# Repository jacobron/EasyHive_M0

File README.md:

# EasyHive_M0
M0-Board Code (Arduino C++) and Hardware Files V1.3

This Board is designed for the purpose of remote and off-grid temperature and weight measurements.

# Features

* ADS1232 ADC-IC for weight reading up to two load-cells
* ATSAMD21G - CortexM0 Microcontroller - programmable with Arduino Software
* Ublox SaraN200 NB-IOT Chip for sending data via narrowband-LTE
* BQ24072 charging IC for USB/Solar and battery temperature monitoring
* DS18B20 temperatur sensor von Maxim Integrated
* Piezo Buzzer and RGB LED for user communication

The board features additional connections for I2S and I2C sensors, which are not used yet.

# copyright
Software: GPL 3.0 and following versions

Hardware: CERN OHL 1.2 and following versions

This files are distributed in the hope that it will be useful,
but WITHOUT ANY WARRANTY; without even the implied warranty of
MERCHANTABILITY or FITNESS FOR A PARTICULAR PURPOSE.
See the GNU General Public License for more details.

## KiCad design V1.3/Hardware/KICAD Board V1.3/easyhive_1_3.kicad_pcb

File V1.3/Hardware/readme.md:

# additional information
* steuckliste is missing some LEDs - we won't use them in production run as nobody see's them in the box ;-)

# copyright
CERN OHL 1.2 and following versions

This files are distributed in the hope that it will be useful,
but WITHOUT ANY WARRANTY; without even the implied warranty of
MERCHANTABILITY or FITNESS FOR A PARTICULAR PURPOSE.
See the GNU General Public License for more details.

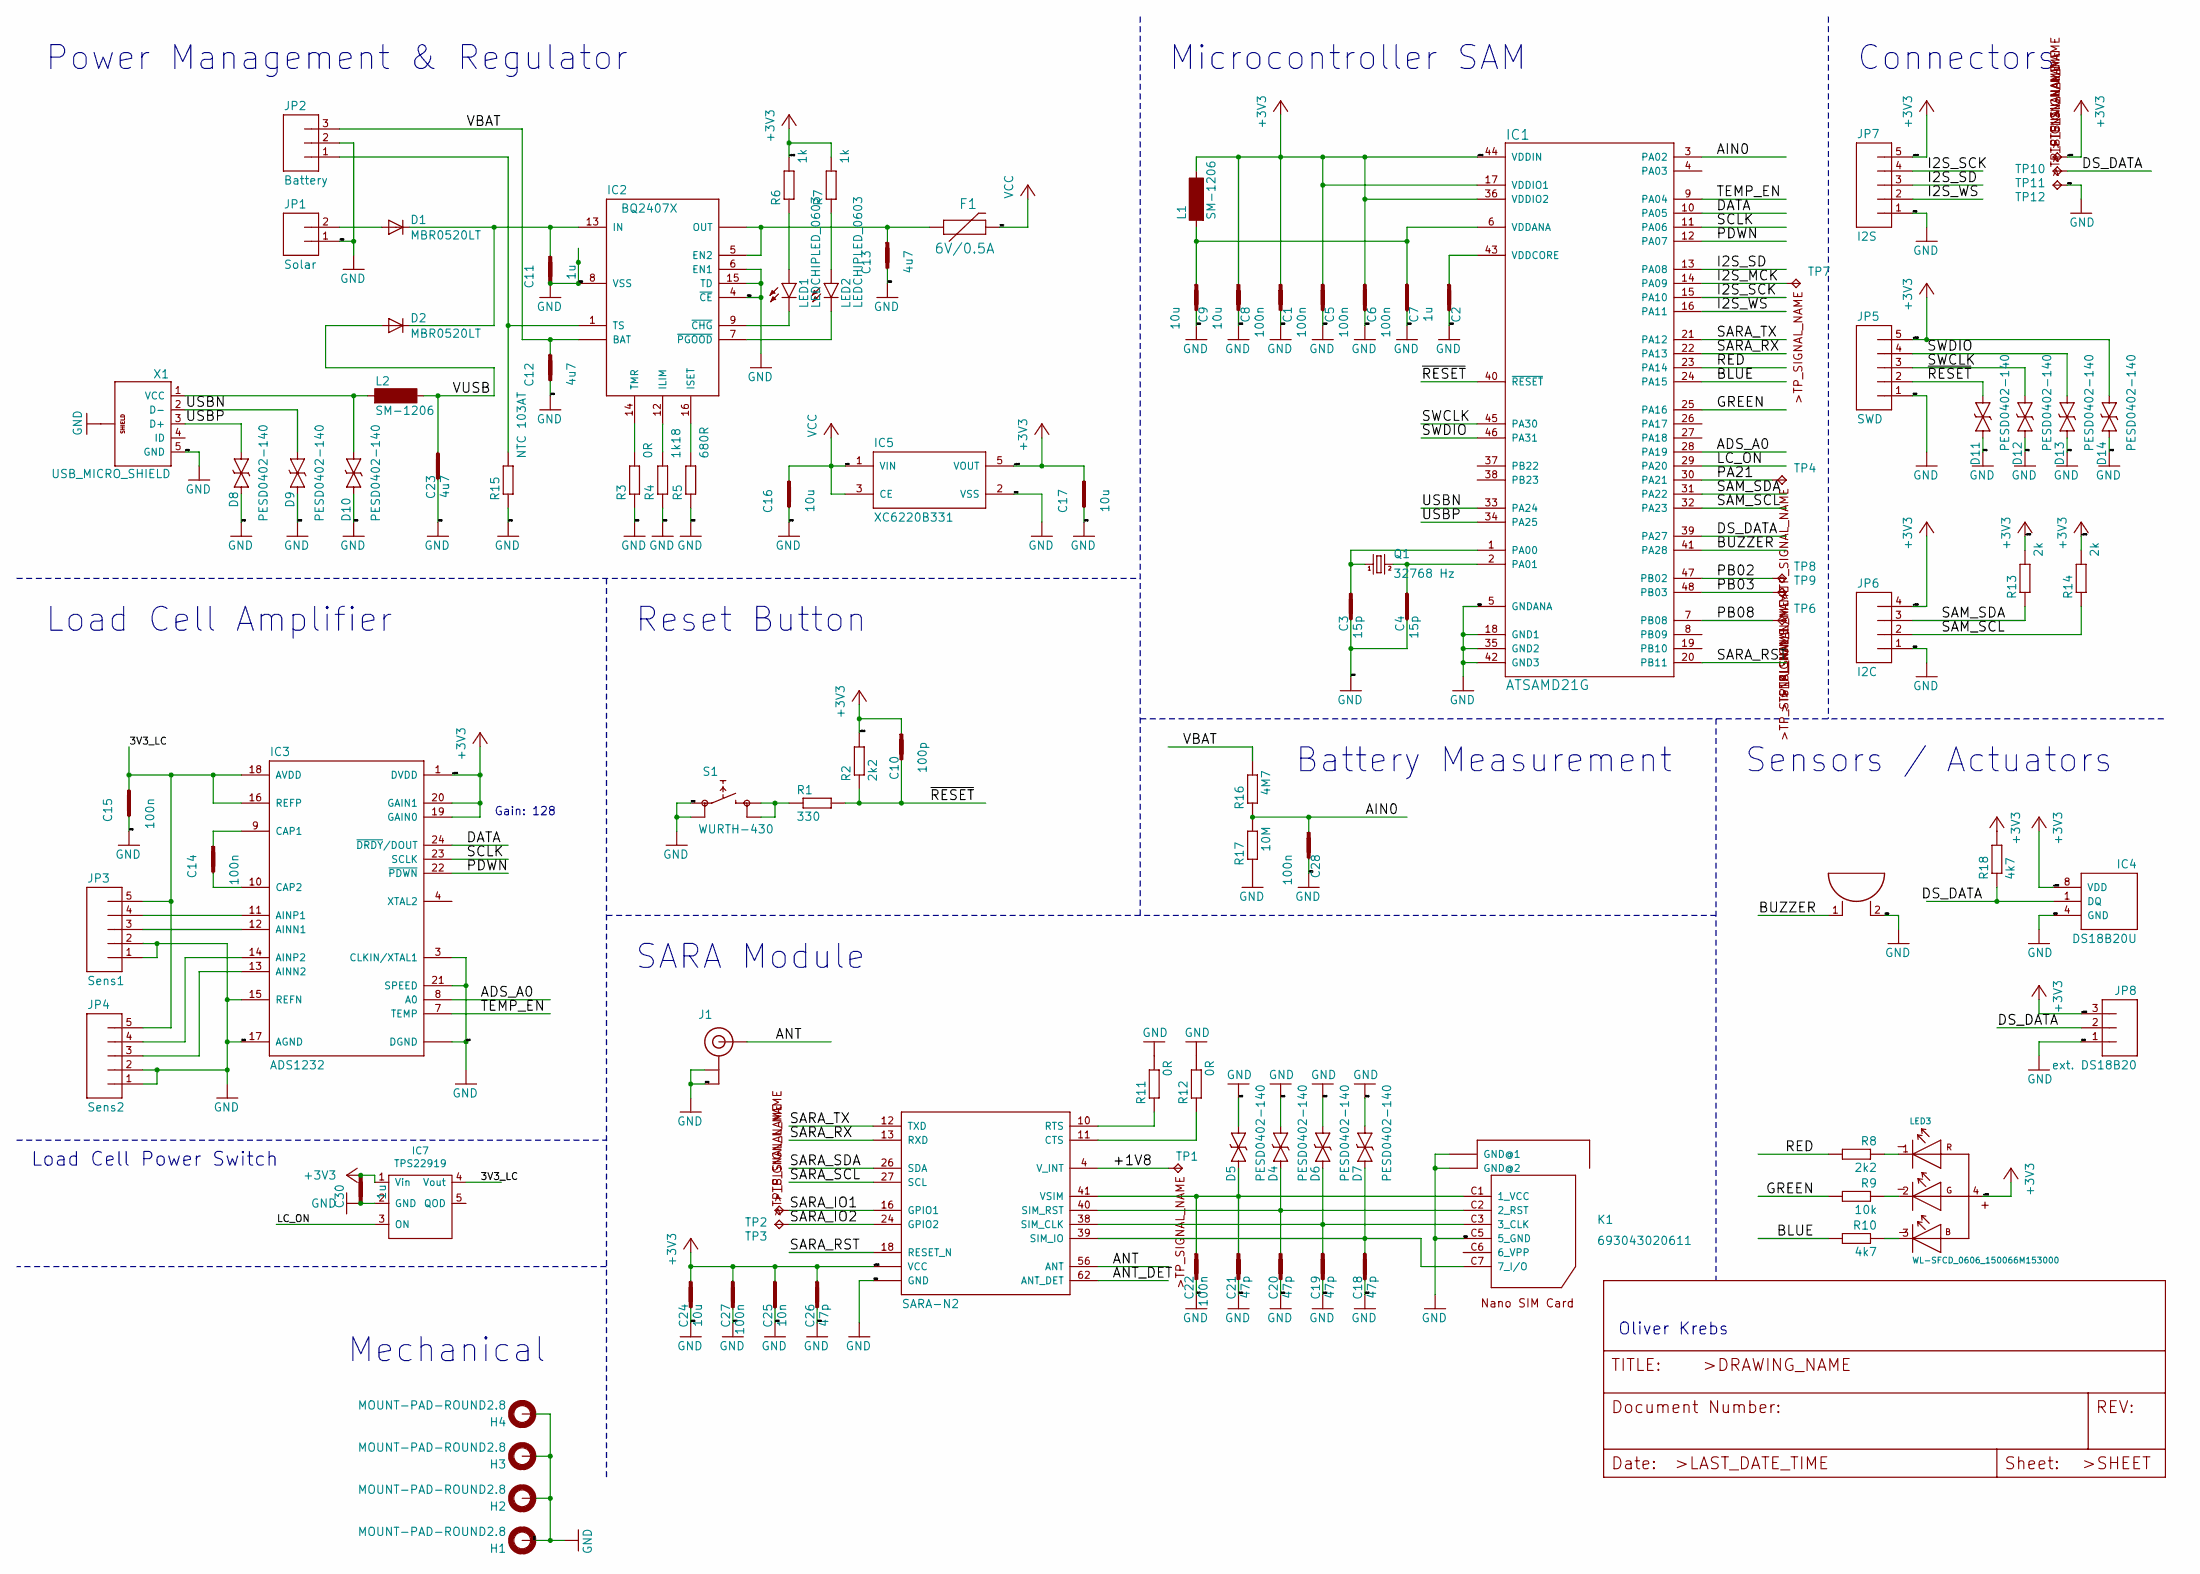
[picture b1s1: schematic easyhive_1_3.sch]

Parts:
C1, C5, C6, C7, C14, C15, C22, C27, C28: 100n; C0402
C2, C11, C30: 1u; C0402
C3, C4: 15p; C0402
C8, C9, C16, C17, C24: 10u; C0402
C10: 100p; C0402
C12, C13, C23: 4u7; C0402
C18, C19, C20, C21, C26: 47p; C0402
C25: 10n; C0402
D1, D2: MBR0520LT; SOD123
D4, D5, D6, D7, D8, D9, D10, D11, D12, D13, D14: PESD0402-140; 0402-TVS
F1: 6V/0.5A; 1206
H1, H2, H3, H4: MOUNT-PAD-ROUND2.8; 2,8-PAD
IC1: ATSAMD21G; TQFP48
IC2: BQ2407X; VQFN16
IC3: ADS1232; TSSOP24
IC4: DS18B20U; UMAX8
IC5: XC6220B331; SOT25
IC6: SARA-N2
IC7: TPS22919; sot-sc70-6
J1: U.FL
JP1: Solar; 1X02_2MM
JP2: Battery; 1X03-2MM
JP3: Sens1; 1X05-2MM
JP4: Sens2; 1X05-2MM
JP5: SWD; 1X05-2MM
JP6: I2C; 1X04-2MM
JP7: I2S; 1X05-2MM
JP8: ext. DS18B20; 1X03-2MM
K1: 693043020611
L1, L2: SM-1206
LED1, LED2: LEDCHIPLED_0603; CHIPLED_0603
LED3: WL-SFCD_0606_150066M153000; WL-SFCX_0606
P1: PKMCS; PKMCS_BUZZER
Q1: 32768 Hz; FC135
R1: 330; C0402
R2, R8: 2k2; C0402
R3, R11, R12: 0R; C0402
R4: 1k18; C0402
R5: 680R; C0402
R6, R7: 1k; C0402
R9: 10k; C0402
R10, R18: 4k7; C0402
R13, R14: 2k; C0402
R15: NTC 103AT; C0402
R16: 4M7; C0402
R17: 10M; C0402
S1: WURTH-430
TP1, TP2, TP3, TP4, TP6, TP7, TP8, TP9, TP10, TP11, TP12: TPTP08R; TP08R
X1: USB_MICRO_SHIELD; USBMICRO

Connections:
+3V3: C1.1, C5.1, C6.1, C8.1, C10.1, C17.1, C24.1, C25.1, C26.1, C27.1, C30.1, D14.P$2 (C), IC1.17 (VDDIO1), IC1.36 (VDDIO2), IC1.44 (VDDIN), IC3.1 (DVDD), IC3.19 (GAIN0), IC3.20 (GAIN1), IC4.8 (VDD), IC5.5 (VOUT), IC6.51 (VCC), IC6.52 (VCC), IC6.53 (VCC), IC7.1 (Vin), JP5.5, JP6.4, JP7.5, JP8.3, L1.2, LED3.4, R2.2, R6.2, R7.2, R13.2, R14.2, R18.2, TP10.TP
/3V3_LC: C15.1, IC3.16 (REFP), IC3.18 (AVDD), IC7.4 (Vout), JP3.5, JP4.5
/+1V8: IC6.4 (V_INT), TP1.TP
/ADS_A0: IC1.28 (PA19), IC3.8 (A0)
/AIN0: C28.1, IC1.3 (PA02), R16.1, R17.2
/ANT: IC6.56 (ANT), J1.P$3 (SIGNAL)
/ANT_DET: IC6.62 (ANT_DET)
/BLUE: IC1.24 (PA15), R10.2
/BUZZER: IC1.41 (PA28), P1.1
/DATA: IC1.10 (PA05), IC3.24 (~DRDY~/DOUT)
/DS_DATA: IC1.39 (PA27), IC4.1 (DQ), JP8.2, R18.1, TP11.TP
/GREEN: IC1.25 (PA16), R9.2
/I2S_MCK: IC1.14 (PA09), TP7.TP
/I2S_SCK: IC1.15 (PA10), JP7.4
/I2S_SD: IC1.13 (PA08), JP7.3
/I2S_WS: IC1.16 (PA11), JP7.2
/LC_ON: IC1.29 (PA20), IC7.3 (ON)
/PA21: IC1.30 (PA21), TP4.TP
/PB02: IC1.47 (PB02), TP8.TP
/PB03: IC1.48 (PB03), TP9.TP
/PB08: IC1.7 (PB08), TP6.TP
/PDWN: IC1.12 (PA07), IC3.22 (~PDWN)
/RED: IC1.23 (PA14), R8.2
/SAM_SCL: IC1.32 (PA23), JP6.2, R14.1
/SAM_SDA: IC1.31 (PA22), JP6.3, R13.1
/SARA_IO1: IC6.16 (GPIO1), TP2.TP
/SARA_IO2: IC6.24 (GPIO2), TP3.TP
/SARA_RST: IC1.20 (PB11), IC6.18 (RESET_N)
/SARA_RX: IC1.22 (PA13), IC6.13 (RXD)
/SARA_SCL: IC6.27 (SCL)
/SARA_SDA: IC6.26 (SDA)
/SARA_TX: IC1.21 (PA12), IC6.12 (TXD)
/SCLK: IC1.11 (PA06), IC3.23 (SCLK)
/SWCLK: D12.P$2 (C), IC1.45 (PA30), JP5.3
/SWDIO: D13.P$2 (C), IC1.46 (PA31), JP5.4
/TEMP_EN: IC1.9 (PA04), IC3.7 (TEMP)
/USBN: D9.P$2 (C), IC1.33 (PA24), X1.2 (D-)
/USBP: D8.P$2 (C), IC1.34 (PA25), X1.3 (D+)
/VBAT: C12.1, IC2.2 (BAT), IC2.3 (BAT), JP2.3, R16.2
/VUSB: C23.1, D2.A, L2.2
/~RESET: C10.2, D11.P$2 (C), IC1.40 (~RESET), JP5.2, R1.2, R2.1
unnamed: C2.1, IC1.43 (VDDCORE)
unnamed: C3.1, IC1.1 (PA00), Q1.1
unnamed: C4.1, IC1.2 (PA01), Q1.2
unnamed: C7.1, C9.1, IC1.6 (VDDANA), L1.1
unnamed: C11.1, D1.C, D2.C, IC2.13 (IN)
unnamed: C13.1, F1.1, IC2.5 (EN2), IC2.10 (OUT), IC2.11 (OUT)
unnamed: C14.1, IC3.9 (CAP1)
unnamed: C14.2, IC3.10 (CAP2)
unnamed: C18.1, D7.P$1 (A), IC6.39 (SIM_IO), K1.C7 (7_I/O)
unnamed: C19.1, D6.P$1 (A), IC6.38 (SIM_CLK), K1.C3 (3_CLK)
unnamed: C20.1, D4.P$1 (A), IC6.40 (SIM_RST), K1.C2 (2_RST)
unnamed: C21.1, C22.1, D5.P$1 (A), IC6.41 (VSIM), K1.C1 (1_VCC)
unnamed: D1.A, JP1.2
unnamed: D10.P$2 (C), L2.1, X1.1 (VCC)
unnamed: IC2.1 (TS), JP2.1, R15.2
unnamed: IC2.7 (~PGOOD), LED2.C
unnamed: IC2.9 (~CHG), LED1.C
unnamed: IC2.12 (ILIM), R4.2
unnamed: IC2.14 (TMR), R3.2
unnamed: IC2.16 (ISET), R5.2
unnamed: IC3.11 (AINP1), JP3.4
unnamed: IC3.12 (AINN1), JP3.3
unnamed: IC3.13 (AINN2), JP4.3
unnamed: IC3.14 (AINP2), JP4.4
unnamed: IC6.10 (RTS), R11.1
unnamed: IC6.11 (CTS), R12.1
unnamed: LED1.A, R6.1
unnamed: LED2.A, R7.1
unnamed: LED3.1 (R), R8.1
unnamed: LED3.2 (G), R9.1
unnamed: LED3.3 (B), R10.1
unnamed: R1.1, S1.2 (1@A), S1.4 (1@B)
VCC: C16.1, F1.2, IC5.1 (VIN), IC5.3 (CE)

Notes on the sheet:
Gain: 128
Oliver Krebs
Power Management & Regulator
Microcontroller SAM
SARA Module
Load Cell Amplifier
Connectors
Sensors / Actuators
Mechanical
Reset Button
Battery Measurement
Load Cell Power Switch

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
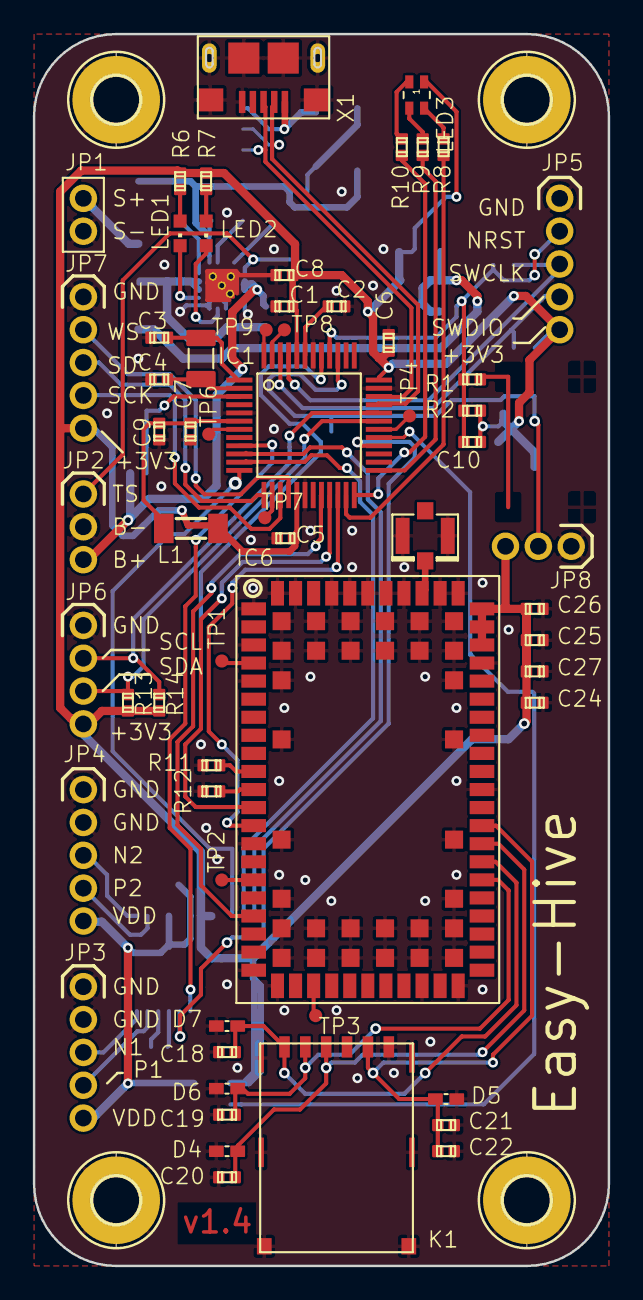
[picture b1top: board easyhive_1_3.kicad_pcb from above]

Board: 2 copper layers, 35.0 x 75.0 mm, 101 parts (0 on the bottom side), 72 nets.

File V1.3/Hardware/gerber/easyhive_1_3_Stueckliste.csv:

"Id","Designator","Package","Quantity","Designation","Manufacturer","Part nr",
1,"IC3","TSSOP24",1,"ADS1232","TI","ADS1232IPWR",
2,"IC1","TQFP48",1,"ATSAMD21G","Microchip Technology","TSAMD21G18A-AUT",
3,"C2,C11,C30","C0402",3,"1u",,,
4,"C3,C4","C0402",2,"15p",,,
5,"C5,C6,C7,C1,C14,C15,C22,C27,C28","C0402",9,"100n",,,
6,"C8,C9,C16,C17,C24","C0402",5,"10u",,,
7,"L1,L2","SM-1206",2,"Ferrite Bead 1k ohm 1LN","WURTH",742792141,"auch anderer Hersteller möglich"
8,"C10","C0402",1,"100p",,,
9,"R1","C0402",1,"330",,,
10,"R2,R8","C0402",2,"2k2",,,
11,,,,,,,
12,"D1,D2","SOD123",2,"DIODE SCHOTTKY 20V 500MA SOD123","ON Semiconductor","MBR0520LT","auch anderer Hersteller möglich"
13,"C12,C13,C23","C0402",3,"4u7",,,
14,"X1","USBMICRO",1,"USB_MICRO_SHIELD","Amphenol ICC","10118193-0001LF",
15,,,,,,,
16,,,,,,,
17,"IC2","VQFN16",1,"BQ2407X","TI","BQ24072RGTT ",
18,"R3,R11,R12","C0402",3,"0R",,,
19,"R4","C0402",1,"1k18",,,
20,"R5","C0402",1,"680R",,,
21,,,,,,,
22,"R6,R7","C0402",2,"1k",,,
23,,,,,,,
24,"R9","C0402",1,"10k",,,
25,"R10,R18","C0402",2,"4k7",,,
26,"Q1","FC135",1,"32768 Hz",,,
27,"IC4","UMAX8",1,"DS18B20U","Maxim Integrated","DS18B20U+",
28,"IC5","SOT25",1,"XC6220B331","Torex Semiconductor","XC6220B331MR-G",
29,"K1","693043020611",1,"SimCard Holder","WÜRTH",693043020611,
30,"IC6","SARA-N2",1,"SARA-N2","U-blox","Sara N200-02B",
31,"C18,C19,C20,C21,C26","C0402",5,"47p",,,
32,"D5,D4,D6,D7,D8,D9,D10,D11,D12,D13,D14","0402-TVS",11,"PESD0402-140","Littlefuse","PESD0402-140","auch anderer Hersteller möglich"
33,"C25","C0402",1,"10n",,,
34,"R13,R14","C0402",2,"2k",,,
35,"F1","1206",1,"6V/0.5A","Bel Fuse Inc","0ZCJ0050FF2G","auch anderer Hersteller möglich"
36,,,,,,,
37,,,,,,,
38,,,,,,,
39,,,,,,,
40,,,,,,,
41,"J1","U.FL",1,"U.FL","Hirose","  U.FL-R-SMT-1(01) ","auch anderer Hersteller möglich"
42,,,,,,,
43,"P1","PKMCS_BUZZER",1,"PKMCS","Murata","PKMCS0909E4000-R1 ",
44,"R16","C0402",1,"4M7",,,
45,"R17","C0402",1,"10M",,,
,,,,,,,
47,"R15","C0402",1,"NTC 103AT 10k","Abracon"," ABNTC-0402-103J-4050F-T ","auch anderer Hersteller möglich"
48,,,,,,,
49,"IC7","sot-sc70-6",1,"TPS22919","TI","TPS22919DCKR",

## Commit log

2020-02-06 major V1.3 release
2020-02-11 documentation
2020-02-11 V1.2 added
